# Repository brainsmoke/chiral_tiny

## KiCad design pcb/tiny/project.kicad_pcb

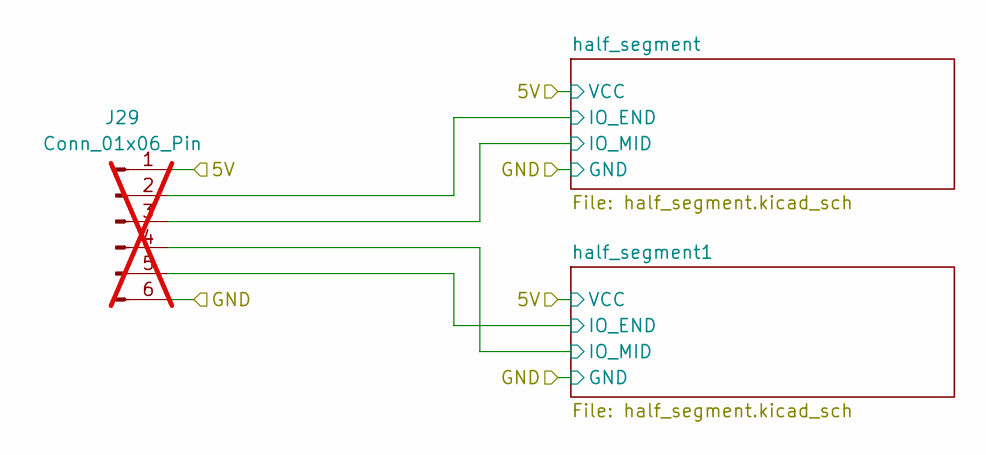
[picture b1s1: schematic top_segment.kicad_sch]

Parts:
J29: Conn_01x06_Pin; th_header6; not fitted

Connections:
/top_segment/5V: J29.1; also elsewhere on the board
/top_segment/GND: J29.6; also elsewhere on the board
/top_segment/half_segment1/IO_END: J29.5; also elsewhere on the board
/top_segment/half_segment1/IO_MID: J29.4; also elsewhere on the board
/top_segment/half_segment/IO_END: J29.2; also elsewhere on the board
/top_segment/half_segment/IO_MID: J29.3; also elsewhere on the board

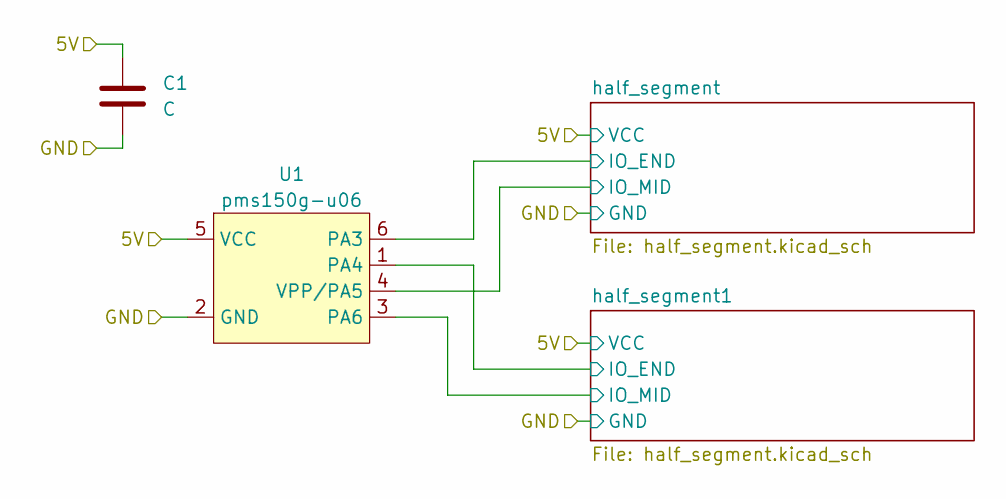
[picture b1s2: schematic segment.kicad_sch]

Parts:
C1: C; C_0402_1005Metric_nosilk; LCSC C52923
U1: pms150g-u06; SOT-23-6; LCSC C49173938

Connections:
/segment/5V: C1.1, U1.5 (VCC); also elsewhere on the board
/segment/GND: C1.2, U1.2 (GND); also elsewhere on the board
/segment/half_segment1/IO_END: U1.1 (PA4); also elsewhere on the board
/segment/half_segment1/IO_MID: U1.3 (PA6); also elsewhere on the board
/segment/half_segment/IO_END: U1.6 (PA3); also elsewhere on the board
/segment/half_segment/IO_MID: U1.4 (VPP/PA5); also elsewhere on the board

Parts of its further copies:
C2, C3, C4, C5, C6: C; C_0402_1005Metric_nosilk; LCSC C52923
U2, U3, U4, U5, U6: pms150g-u06; SOT-23-6; LCSC C49173938

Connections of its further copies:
/segment1/5V: C2.1, U2.5 (VCC); also elsewhere on the board
/segment1/GND: C2.2, U2.2 (GND); also elsewhere on the board
/segment1/half_segment1/IO_END: U2.1 (PA4); also elsewhere on the board
/segment1/half_segment1/IO_MID: U2.3 (PA6); also elsewhere on the board
/segment1/half_segment/IO_END: U2.6 (PA3); also elsewhere on the board
/segment1/half_segment/IO_MID: U2.4 (VPP/PA5); also elsewhere on the board
/segment2/5V: C3.1, U3.5 (VCC); also elsewhere on the board
/segment2/GND: C3.2, U3.2 (GND); also elsewhere on the board
/segment2/half_segment1/IO_END: U3.1 (PA4); also elsewhere on the board
/segment2/half_segment1/IO_MID: U3.3 (PA6); also elsewhere on the board
/segment2/half_segment/IO_END: U3.6 (PA3); also elsewhere on the board
/segment2/half_segment/IO_MID: U3.4 (VPP/PA5); also elsewhere on the board
/segment3/5V: C4.1, U4.5 (VCC); also elsewhere on the board
/segment3/GND: C4.2, U4.2 (GND); also elsewhere on the board
/segment3/half_segment1/IO_END: U4.1 (PA4); also elsewhere on the board
/segment3/half_segment1/IO_MID: U4.3 (PA6); also elsewhere on the board
/segment3/half_segment/IO_END: U4.6 (PA3); also elsewhere on the board
/segment3/half_segment/IO_MID: U4.4 (VPP/PA5); also elsewhere on the board
/segment4/5V: C5.1, U5.5 (VCC); also elsewhere on the board
/segment4/GND: C5.2, U5.2 (GND); also elsewhere on the board
/segment4/half_segment1/IO_END: U5.1 (PA4); also elsewhere on the board
/segment4/half_segment1/IO_MID: U5.3 (PA6); also elsewhere on the board
/segment4/half_segment/IO_END: U5.6 (PA3); also elsewhere on the board
/segment4/half_segment/IO_MID: U5.4 (VPP/PA5); also elsewhere on the board
/segment5/5V: C6.1, U6.5 (VCC); also elsewhere on the board
/segment5/GND: C6.2, U6.2 (GND); also elsewhere on the board
/segment5/half_segment1/IO_END: U6.1 (PA4); also elsewhere on the board
/segment5/half_segment1/IO_MID: U6.3 (PA6); also elsewhere on the board
/segment5/half_segment/IO_END: U6.6 (PA3); also elsewhere on the board
/segment5/half_segment/IO_MID: U6.4 (VPP/PA5); also elsewhere on the board

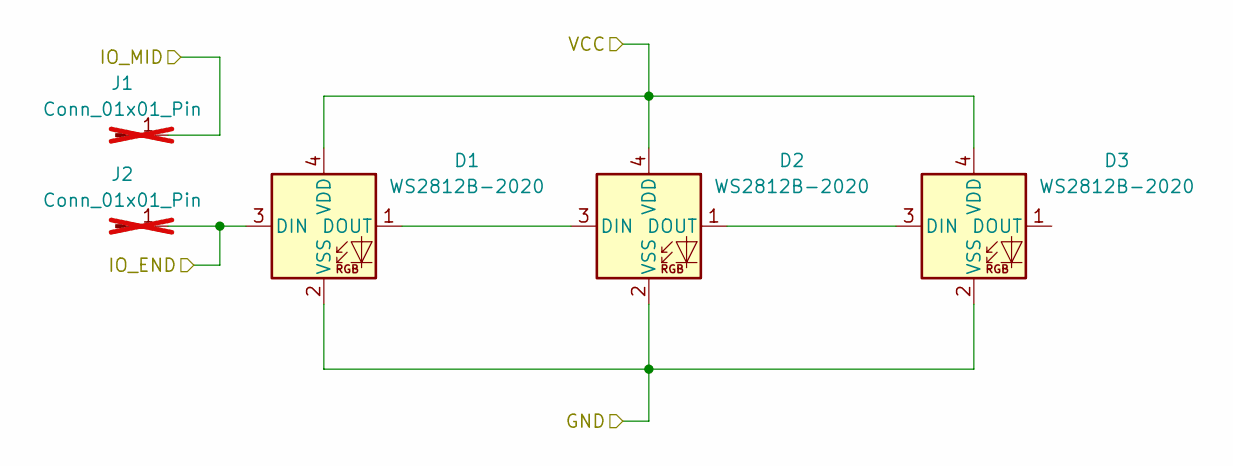
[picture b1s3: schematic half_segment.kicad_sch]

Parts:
D1, D2, D3: WS2812B-2020; LED_WS2812B-2020_PLCC4_2.0x2.0mm; LCSC C55109522
J1, J2: Conn_01x01_Pin; th_pad; not fitted

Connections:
/segment/5V: D1.4 (VDD), D2.4 (VDD), D3.4 (VDD); also elsewhere on the board
/segment/GND: D1.2 (VSS), D2.2 (VSS), D3.2 (VSS); also elsewhere on the board
/segment/half_segment/IO_END: D1.3 (DIN), J2.1; also elsewhere on the board
/segment/half_segment/IO_MID: J1.1; also elsewhere on the board
unnamed: D1.1 (DOUT), D2.3 (DIN)
unnamed: D2.1 (DOUT), D3.3 (DIN)

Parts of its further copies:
D4, D5, D6, D7, D8, D9, D10, D11, D12, D13, D14, D15, D16, D17, D18, D19, D20, D21, D22, D23, D24, D25, D26, D27, D28, D29, D30, D31, D32, D33, D34, D35, D36, D37, D38, D39, D40, D41, D42: WS2812B-2020; LED_WS2812B-2020_PLCC4_2.0x2.0mm; LCSC C55109522
J3, J4, J5, J6, J7, J8, J9, J10, J11, J12, J13, J14, J15, J16, J17, J18, J19, J20, J21, J22, J23, J24, J25, J26, J27, J28: Conn_01x01_Pin; th_pad; not fitted

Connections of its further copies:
/segment1/5V: D7.4 (VDD), D8.4 (VDD), D9.4 (VDD), D10.4 (VDD), D11.4 (VDD), D12.4 (VDD); also elsewhere on the board
/segment1/GND: D7.2 (VSS), D8.2 (VSS), D9.2 (VSS), D10.2 (VSS), D11.2 (VSS), D12.2 (VSS); also elsewhere on the board
/segment1/half_segment1/IO_END: D7.3 (DIN), J6.1; also elsewhere on the board
/segment1/half_segment1/IO_MID: J5.1; also elsewhere on the board
/segment1/half_segment/IO_END: D10.3 (DIN), J8.1; also elsewhere on the board
/segment1/half_segment/IO_MID: J7.1; also elsewhere on the board
/segment2/5V: D13.4 (VDD), D14.4 (VDD), D15.4 (VDD), D16.4 (VDD), D17.4 (VDD), D18.4 (VDD); also elsewhere on the board
/segment2/GND: D13.2 (VSS), D14.2 (VSS), D15.2 (VSS), D16.2 (VSS), D17.2 (VSS), D18.2 (VSS); also elsewhere on the board
/segment2/half_segment1/IO_END: D13.3 (DIN), J10.1; also elsewhere on the board
/segment2/half_segment1/IO_MID: J9.1; also elsewhere on the board
/segment2/half_segment/IO_END: D16.3 (DIN), J12.1; also elsewhere on the board
/segment2/half_segment/IO_MID: J11.1; also elsewhere on the board
/segment3/5V: D19.4 (VDD), D20.4 (VDD), D21.4 (VDD), D22.4 (VDD), D23.4 (VDD), D24.4 (VDD); also elsewhere on the board
/segment3/GND: D19.2 (VSS), D20.2 (VSS), D21.2 (VSS), D22.2 (VSS), D23.2 (VSS), D24.2 (VSS); also elsewhere on the board
/segment3/half_segment1/IO_END: D19.3 (DIN), J14.1; also elsewhere on the board
/segment3/half_segment1/IO_MID: J13.1; also elsewhere on the board
/segment3/half_segment/IO_END: D22.3 (DIN), J16.1; also elsewhere on the board
/segment3/half_segment/IO_MID: J15.1; also elsewhere on the board
/segment4/5V: D31.4 (VDD), D32.4 (VDD), D33.4 (VDD), D34.4 (VDD), D35.4 (VDD), D36.4 (VDD); also elsewhere on the board
/segment4/GND: D31.2 (VSS), D32.2 (VSS), D33.2 (VSS), D34.2 (VSS), D35.2 (VSS), D36.2 (VSS); also elsewhere on the board
/segment4/half_segment1/IO_END: D31.3 (DIN), J22.1; also elsewhere on the board
/segment4/half_segment1/IO_MID: J21.1; also elsewhere on the board
/segment4/half_segment/IO_END: D34.3 (DIN), J24.1; also elsewhere on the board
/segment4/half_segment/IO_MID: J23.1; also elsewhere on the board
/segment5/5V: D37.4 (VDD), D38.4 (VDD), D39.4 (VDD), D40.4 (VDD), D41.4 (VDD), D42.4 (VDD); also elsewhere on the board
/segment5/GND: D37.2 (VSS), D38.2 (VSS), D39.2 (VSS), D40.2 (VSS), D41.2 (VSS), D42.2 (VSS); also elsewhere on the board
/segment5/half_segment1/IO_END: D37.3 (DIN), J26.1; also elsewhere on the board
/segment5/half_segment1/IO_MID: J25.1; also elsewhere on the board
/segment5/half_segment/IO_END: D40.3 (DIN), J28.1; also elsewhere on the board
/segment5/half_segment/IO_MID: J27.1; also elsewhere on the board
/segment/5V: D4.4 (VDD), D5.4 (VDD), D6.4 (VDD); also elsewhere on the board
/segment/GND: D4.2 (VSS), D5.2 (VSS), D6.2 (VSS); also elsewhere on the board
/segment/half_segment1/IO_END: D4.3 (DIN), J4.1; also elsewhere on the board
/segment/half_segment1/IO_MID: J3.1; also elsewhere on the board
/top_segment/5V: D25.4 (VDD), D26.4 (VDD), D27.4 (VDD), D28.4 (VDD), D29.4 (VDD), D30.4 (VDD); also elsewhere on the board
/top_segment/GND: D25.2 (VSS), D26.2 (VSS), D27.2 (VSS), D28.2 (VSS), D29.2 (VSS), D30.2 (VSS); also elsewhere on the board
/top_segment/half_segment1/IO_END: D28.3 (DIN), J20.1; also elsewhere on the board
/top_segment/half_segment1/IO_MID: J19.1; also elsewhere on the board
/top_segment/half_segment/IO_END: D25.3 (DIN), J18.1; also elsewhere on the board
/top_segment/half_segment/IO_MID: J17.1; also elsewhere on the board
unnamed: D4.1 (DOUT), D5.3 (DIN)
unnamed: D5.1 (DOUT), D6.3 (DIN)
unnamed: D7.1 (DOUT), D8.3 (DIN)
unnamed: D8.1 (DOUT), D9.3 (DIN)
unnamed: D10.1 (DOUT), D11.3 (DIN)
unnamed: D11.1 (DOUT), D12.3 (DIN)
unnamed: D13.1 (DOUT), D14.3 (DIN)
unnamed: D14.1 (DOUT), D15.3 (DIN)
unnamed: D16.1 (DOUT), D17.3 (DIN)
unnamed: D17.1 (DOUT), D18.3 (DIN)
unnamed: D19.1 (DOUT), D20.3 (DIN)
unnamed: D20.1 (DOUT), D21.3 (DIN)
unnamed: D22.1 (DOUT), D23.3 (DIN)
unnamed: D23.1 (DOUT), D24.3 (DIN)
unnamed: D25.1 (DOUT), D26.3 (DIN)
unnamed: D26.1 (DOUT), D27.3 (DIN)
unnamed: D28.1 (DOUT), D29.3 (DIN)
unnamed: D29.1 (DOUT), D30.3 (DIN)
unnamed: D31.1 (DOUT), D32.3 (DIN)
unnamed: D32.1 (DOUT), D33.3 (DIN)
unnamed: D34.1 (DOUT), D35.3 (DIN)
unnamed: D35.1 (DOUT), D36.3 (DIN)
unnamed: D37.1 (DOUT), D38.3 (DIN)
unnamed: D38.1 (DOUT), D39.3 (DIN)
unnamed: D40.1 (DOUT), D41.3 (DIN)
unnamed: D41.1 (DOUT), D42.3 (DIN)

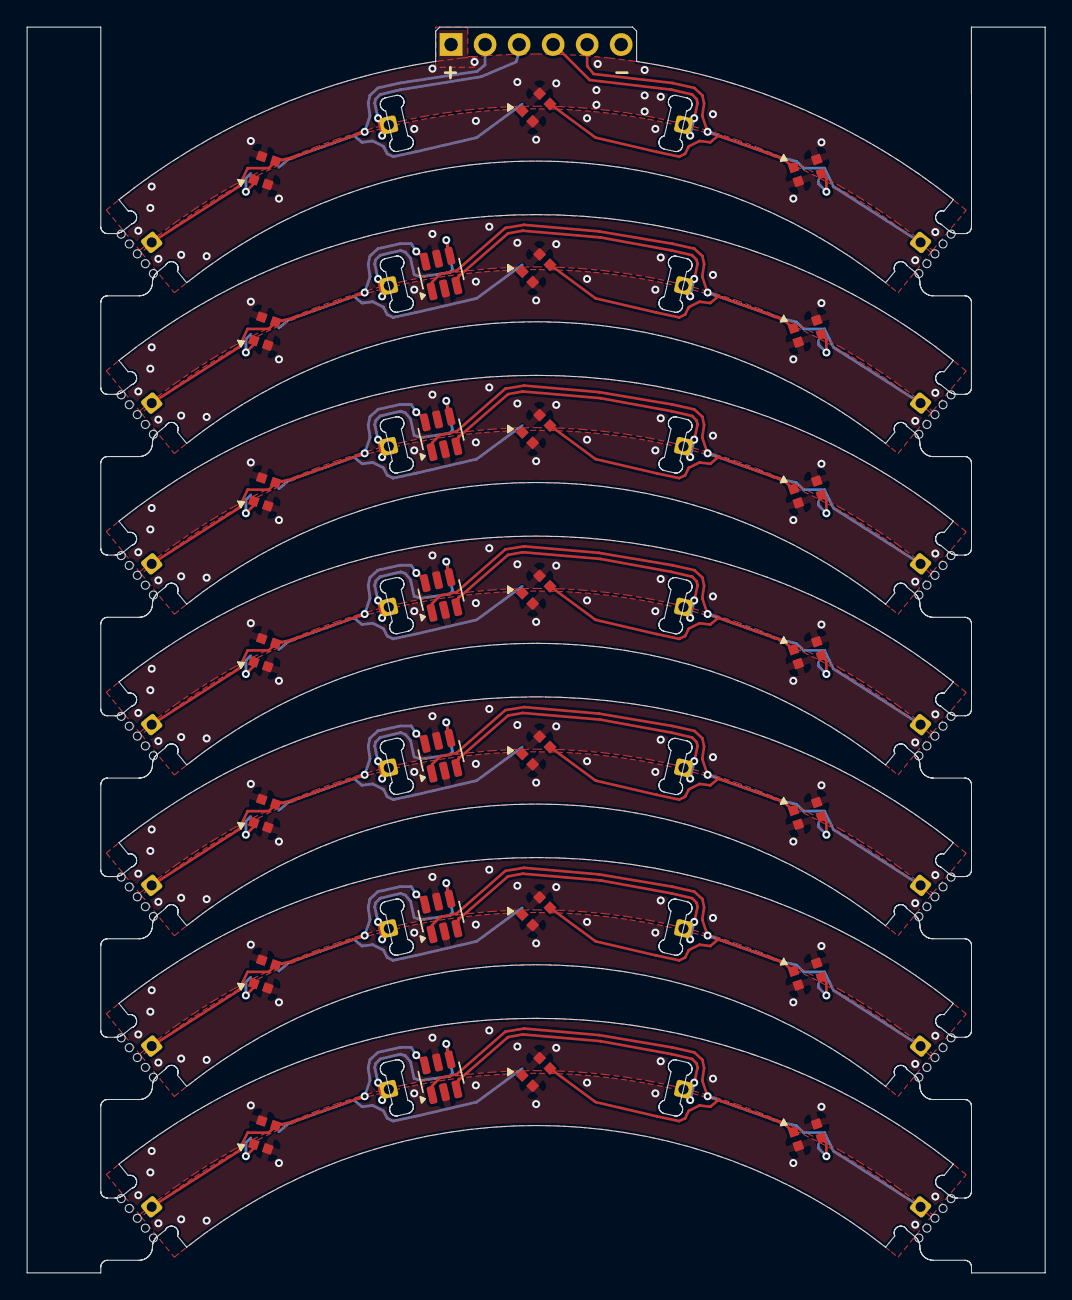
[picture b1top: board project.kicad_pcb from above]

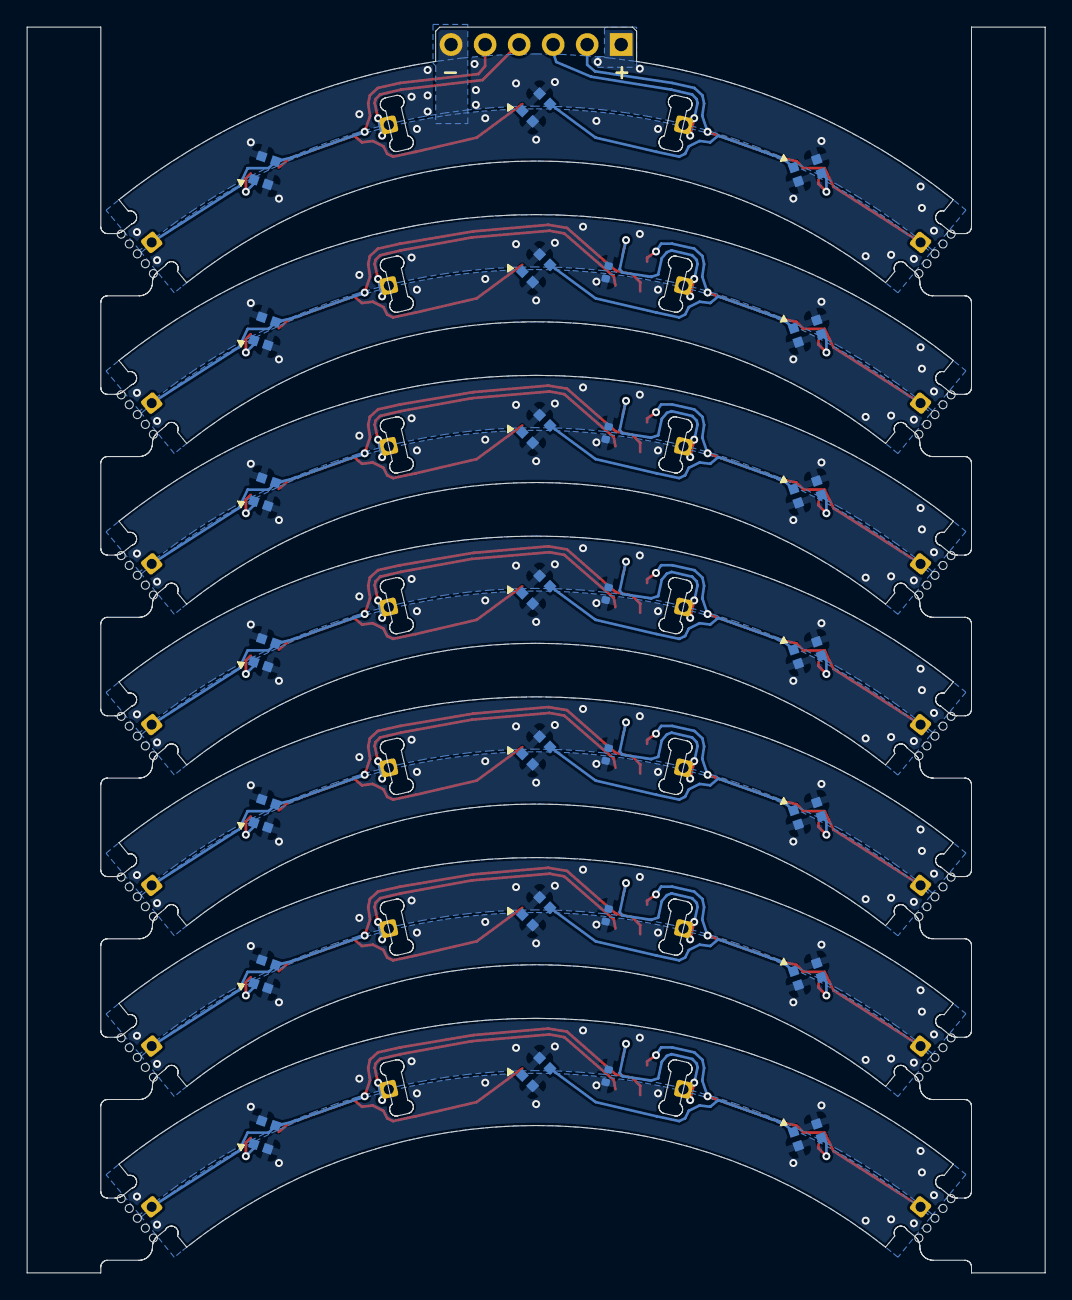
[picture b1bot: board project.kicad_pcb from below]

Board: 2 copper layers, 76.0 x 93.0 mm, 83 parts (41 on the bottom side), 70 nets.
